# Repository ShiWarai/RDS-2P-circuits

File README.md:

# RDS-2P Circuits

Электрические схемы для робота [RDS-2P](https://github.com/ShiWarai/RDS-2P), разработанные для лабораторного или домашнего химического травления с использованием бытовой химии.

<table>
<tr>
<td align="center" valign="middle"></td>
<td align="center" valign="middle"></td>
</tr>
<tr>
<td></td>
<td></td>
</tr>
</table>

## Описание плат

- **Плата питания для RDS-2P** устанавливается в заднем отсеке робота и **питает** узлы робота.
- **Плата коммутации двигателей для RDS-2P** выполняет распределительную (силовую коммутационную) функцию и **сокращает количество** проводов.

## Компоненты

### Плата питания для RDS-2P

| Имя | Кол-во | Изображение | Примечание |
|-----|--------|-------------|------------|
| XT30U | 6 |  | Лучше покупать парами |
| XY301V-A-5.0-2P | 3 |  | Можно заменить на провода с разъёмами |
| BMS 2S 20A, защита Li-ion с балансировкой | 1 |  | <a href="https://www.ozon.ru/product/bms-2s-20a-plata-zashchity-s-balansirovkoy-1sht-kontroller-zaryada-li-ion-batarey-s-balansirovkoy-1929224672/">Ozon</a> |
| DC-DC понижающий LM2596S, 8–40 V → 5 V | 2 |  | <a href="https://www.ozon.ru/product/ponizhayushchiy-preobrazovatel-dc-dc-8-40v-na-5v-lm2596s-stabilizator-5v-2sht-2024449951/">Ozon</a> |

### Плата коммутации двигателей для RDS-2P

| Имя | Кол-во | Изображение | Примечание |
|-----|--------|-------------|------------|
| 5264-3AW (клеммник, 3 контакта) | 4 |  |  |
| XT30U | 1 |  | Лучше покупать парами |
| XY301V-A-5.0-2P | 1 |  | Можно заменить на провода с разъёмами |

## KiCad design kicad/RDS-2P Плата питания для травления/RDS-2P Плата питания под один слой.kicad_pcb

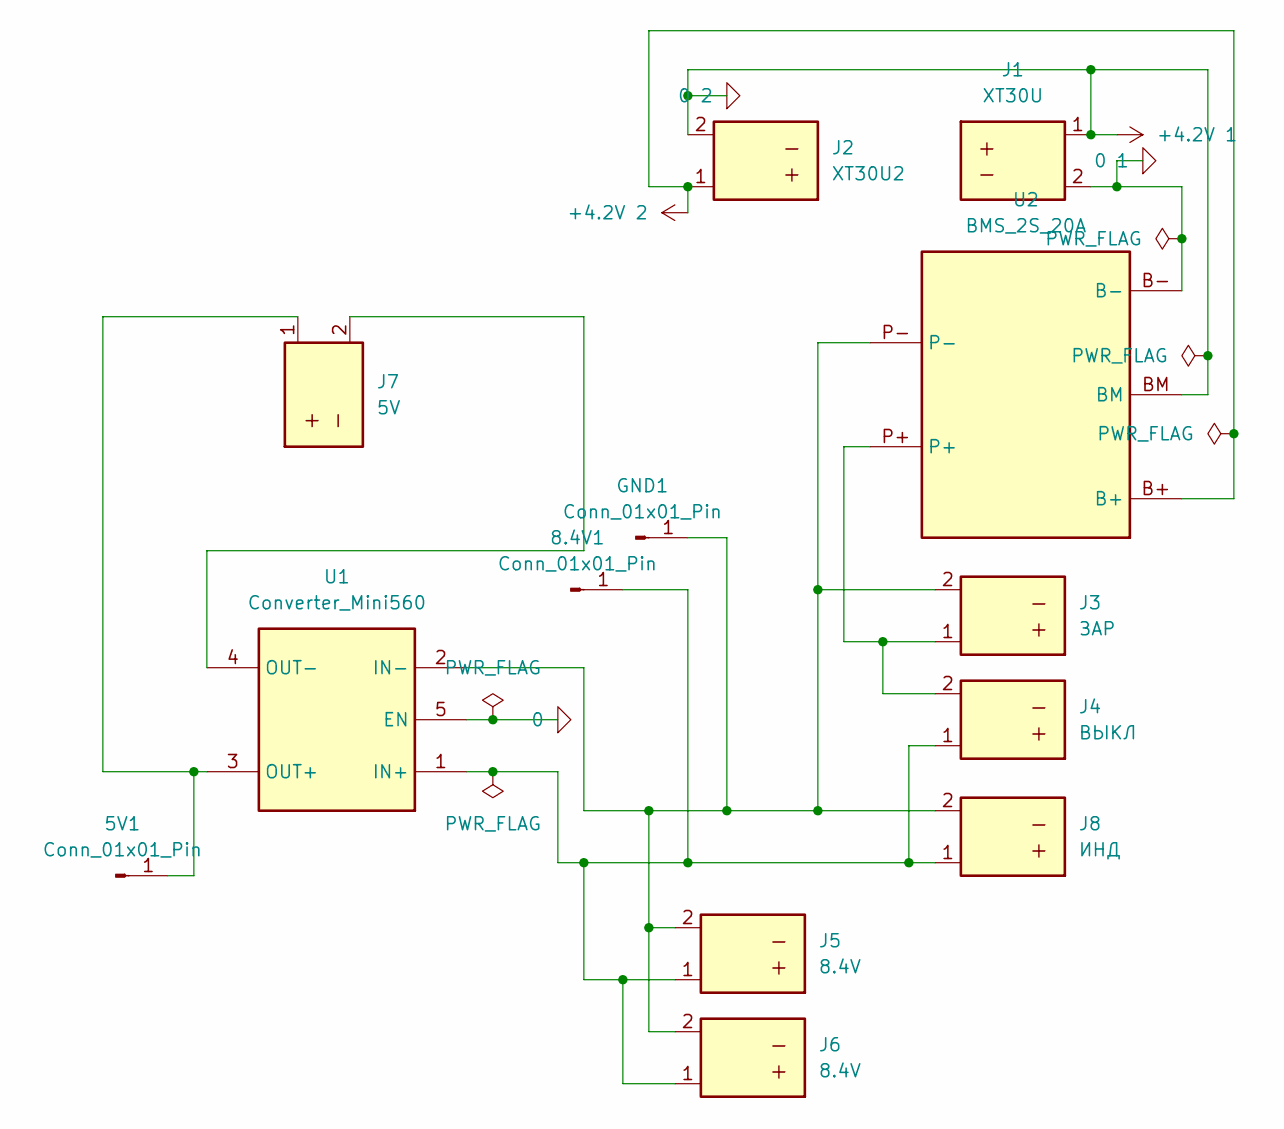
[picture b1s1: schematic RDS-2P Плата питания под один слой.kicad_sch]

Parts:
5V1, 8.4V1: Conn_01x01_Pin; PinSocket_1x01_P2.54mm_Vertical
GND1: Conn_01x01_Pin; PinSocket_1x01_P2.54mm_Vertical
J1: XT30U; AMASS_XT30U-power_1x02_P5.0mm_Vertical
J2: XT30U2; AMASS_XT30U-power_1x02_P5.0mm_Vertical
J3: ЗАР; AMASS_XT30U-power_1x02_P5.0mm_Vertical
J4: ВЫКЛ; AMASS_XT30U-power_1x02_P5.0mm_Vertical
J5, J6: 8.4V; AMASS_XT30U-power_1x02_P5.0mm_Vertical
J7: 5V; AMASS_XT30U-power_1x02_P5.0mm_Vertical
J8: ИНД; AMASS_XT30U-power_1x02_P5.0mm_Vertical
U1: Converter_Mini560; Regulator_Mini560_5V
U2: BMS_2S_20A

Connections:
0: U1.5 (EN)
0 1: J1.2, U2.B-
+4.2V 1: J1.1, J2.2, U2.BM
+4.2V 2: J2.1, U2.B+
unnamed: 5V1.1, J7.1, U1.3 (OUT+)
unnamed: 8.4V1.1, J4.1, J5.1, J6.1, J8.1, U1.1 (IN+)
unnamed: GND1.1, J3.2, J5.2, J6.2, J8.2, U1.2 (IN-), U2.P-
unnamed: J3.1, J4.2, U2.P+
unnamed: J7.2, U1.4 (OUT-)

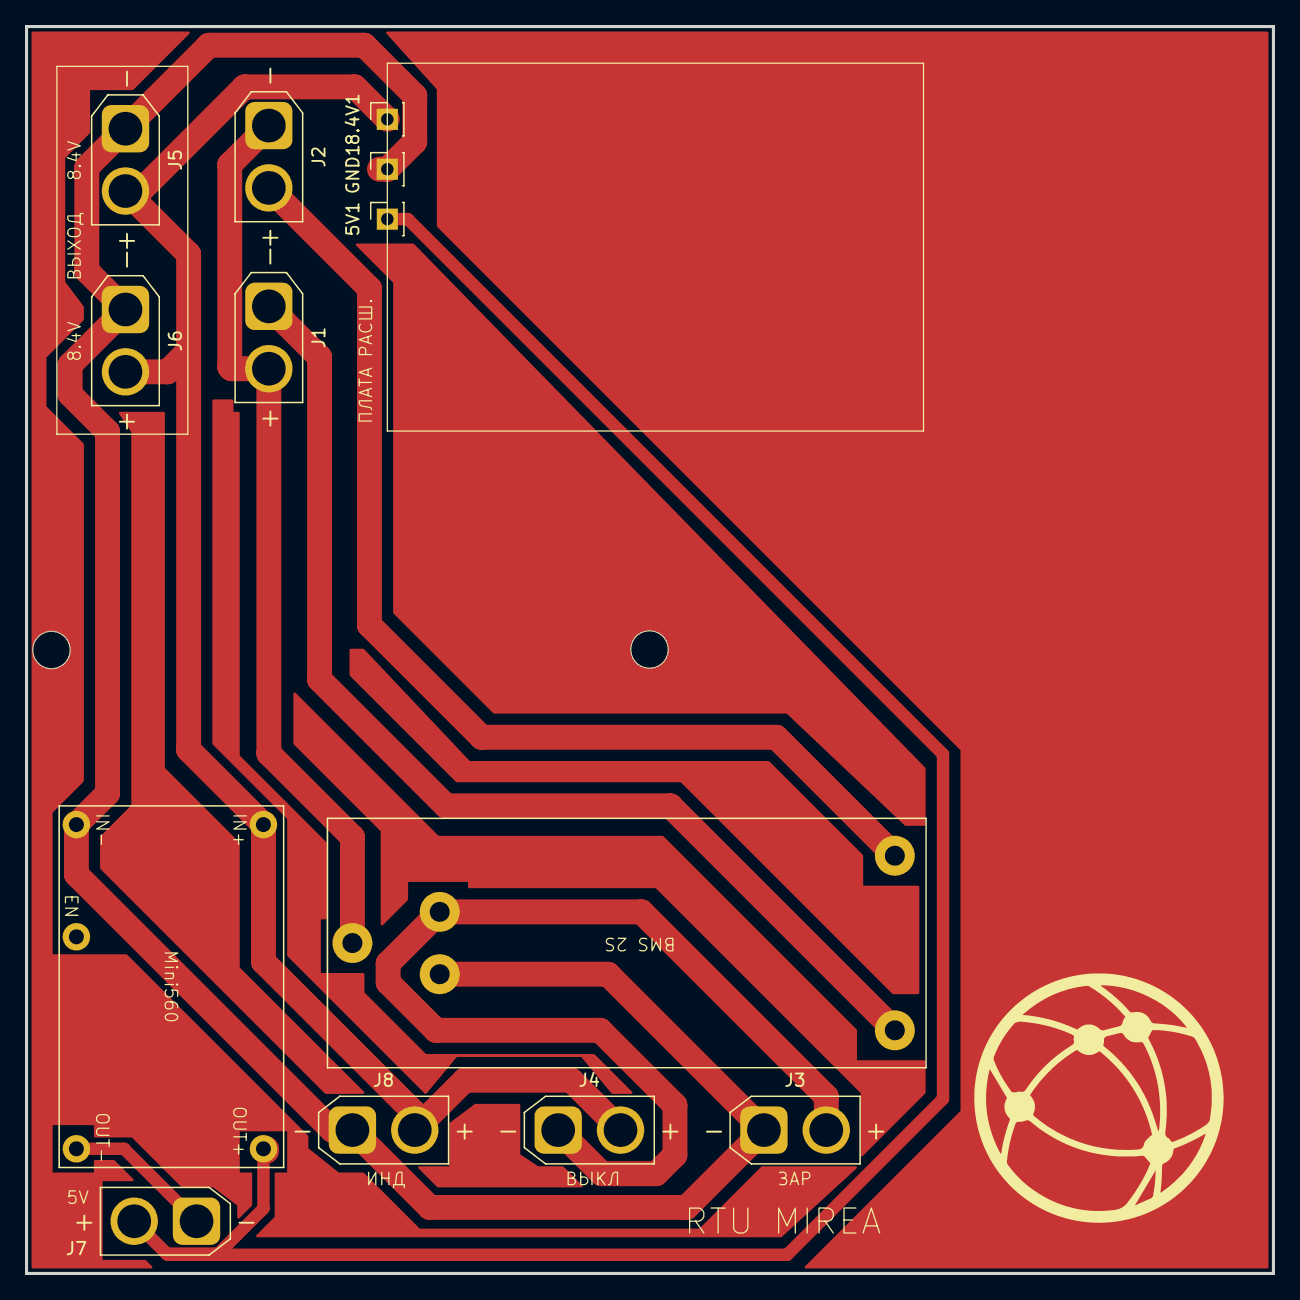
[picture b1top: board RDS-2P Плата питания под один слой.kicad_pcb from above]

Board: 2 copper layers, 100.0 x 100.0 mm, 15 parts (0 on the bottom side), 8 nets.

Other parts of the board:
Pad_gge17218: Pad_gge17218
Pad_gge17221: Pad_gge17221

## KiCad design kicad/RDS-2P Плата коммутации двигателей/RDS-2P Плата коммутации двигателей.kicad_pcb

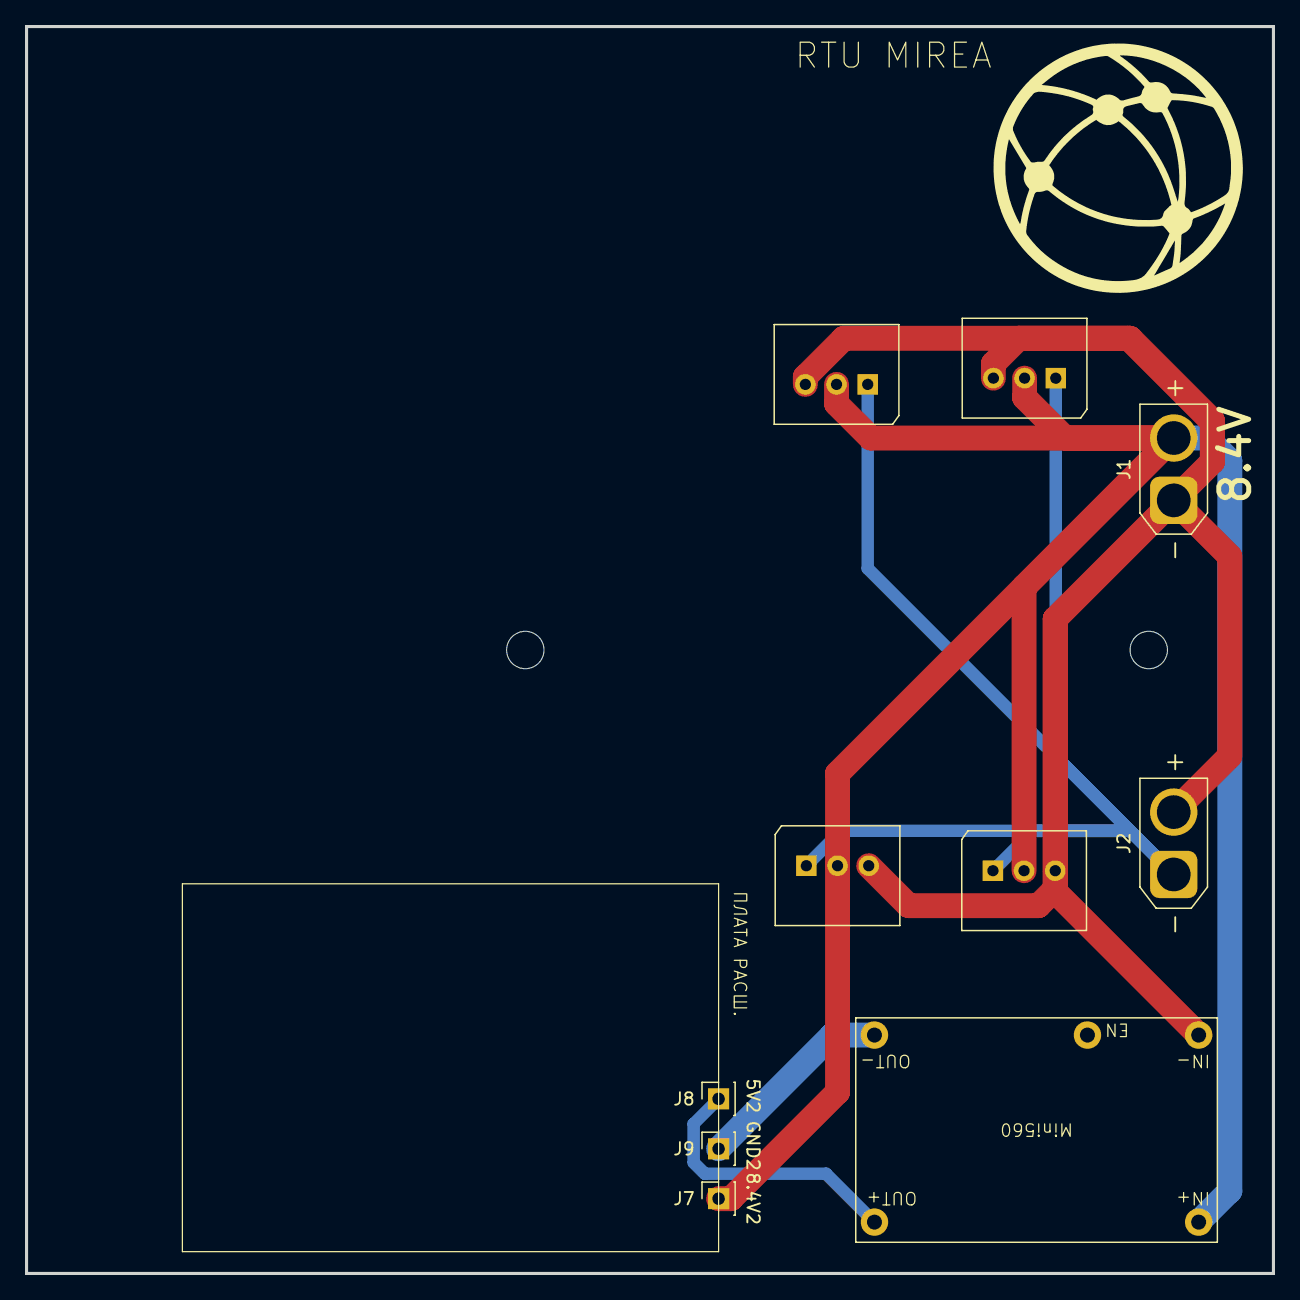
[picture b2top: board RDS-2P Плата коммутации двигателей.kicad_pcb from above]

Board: 2 copper layers, 100.0 x 100.0 mm, 12 parts (0 on the bottom side), 5 nets.

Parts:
Hole_gge19228: Hole_gge19228
Hole_gge19243: Hole_gge19243
J1, J2: XT30U; AMASS_XT30U-power_1x02_P5.0mm_Vertical
J3, J4, J5, J6: 5264-3AW; Molex_Mini-SPOX_5264-3AW
J7, J8, J9: Conn_01x01_Pin; PinSocket_1x01_P2.54mm_Vertical
U1: Converter_Mini560; Regulator_Mini560_5V

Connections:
0: J1.2, J2.1, J3.3, J4.3, J5.3, J6.3, U1.2 (IN-)
+8.4V: J1.1, J3.2, J4.2, J5.2, J6.2, J7.1, U1.1 (IN+)
unnamed: J2.2, J3.1, J4.1, J5.1, J6.1
unnamed: J8.1, U1.3 (OUT+)
unnamed: J9.1, U1.4 (OUT-)

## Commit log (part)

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2025-03-06 Build: перенос проекта с GitLab
2025-03-06 Docs: обновлены ссылки
2026-03-20 Fix: переместил на правильные слои элементы
2026-03-20 Fix: поменял местами неправильные надписи
2026-03-21 Docs: добавлены изображения и информация о платах
2026-03-21 Docs: добавлена информация по компонентам
2026-03-21 Docs: уточнил информацию и обновил изображение
2026-03-21 Docs: удалена информация генеративная
